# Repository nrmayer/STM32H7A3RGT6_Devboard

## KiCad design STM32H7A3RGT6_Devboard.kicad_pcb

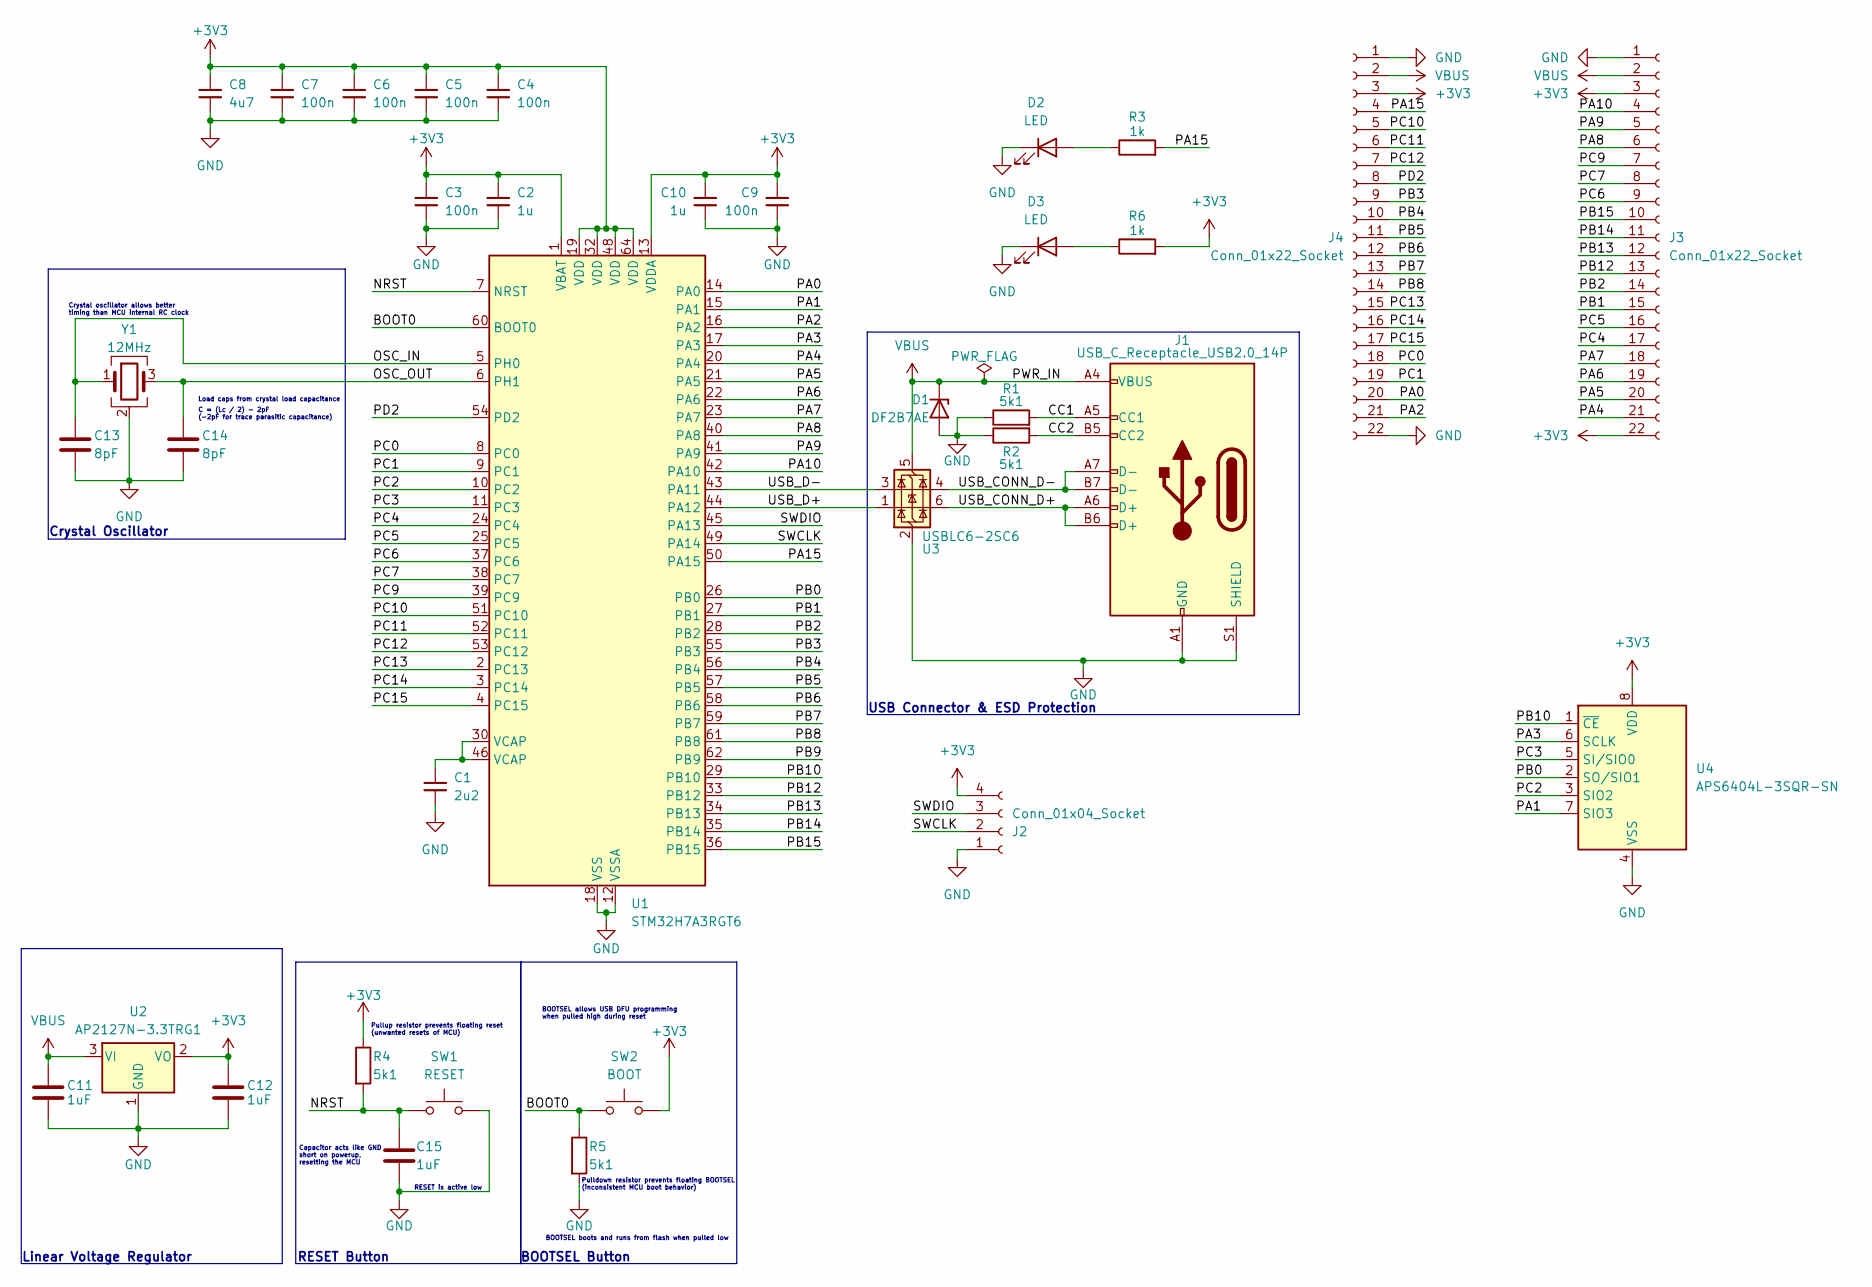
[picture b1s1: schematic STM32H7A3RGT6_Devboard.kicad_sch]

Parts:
C1: 2u2; C_0402_1005Metric_Pad0.74x0.62mm_HandSolder
C2, C10: 1u; C_0603_1608Metric
C3, C4, C5, C6, C7, C9: 100n; C_0402_1005Metric_Pad0.74x0.62mm_HandSolder
C8: 4u7; C_0603_1608Metric
C11, C12: 1uF; C_0402_1005Metric_Pad0.74x0.62mm_HandSolder
C13, C14: 8pF; C_0402_1005Metric_Pad0.74x0.62mm_HandSolder
C15: 1uF; C_0603_1608Metric_Pad1.08x0.95mm_HandSolder
D1: DF2B7AE; D_SOD-523
D2, D3: LED; LED_0603_1608Metric
J1: USB_C_Receptacle_USB2.0_14P; USB_C_Receptacle_Molex_217179-0001
J2: Conn_01x04_Socket; PinHeader_1x04_P2.54mm_Vertical
J3, J4: Conn_01x22_Socket; PinHeader_1x22_P2.54mm_Vertical
R1, R2, R4, R5: 5k1; R_0603_1608Metric
R3, R6: 1k; R_0603_1608Metric_Pad0.98x0.95mm_HandSolder
SW1: RESET; SW_Push_1P1T-SH_NO_CK_KMR2xxG
SW2: BOOT; SW_Push_1P1T-SH_NO_CK_KMR2xxG
U1: STM32H7A3RGT6; LQFP-64_10x10mm_P0.5mm
U2: AP2127N-3.3TRG1; SOT-23
U3: USBLC6-2SC6; SOT-23-6
U4: APS6404L-3SQR-SN; SOIC-8_3.9x4.9mm_P1.27mm
Y1: 12MHz; Crystal_SMD_2016-4Pin_2.0x1.6mm

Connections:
+3V3: C2.1, C3.1, C4.1, C5.1, C6.1, C7.1, C8.1, C9.1, C10.1, C12.1, J2.4, J3.3, J3.22, J4.3, R4.1, R6.2, SW2.2, U1.1 (VBAT), U1.13 (VDDA), U1.19 (VDD), U1.32 (VDD), U1.48 (VDD), U1.64 (VDD), U2.2 (VO), U4.8 (VDD)
/BOOT0: R5.1, SW2.1, U1.60 (BOOT0)
/CC1: J1.A5 (CC1), R1.2
/CC2: J1.B5 (CC2), R2.2
/NRST: C15.1, R4.2, SW1.1, U1.7 (NRST)
/OSC_IN: C13.1, U1.5 (PH0), Y1.1
/OSC_OUT: C14.1, U1.6 (PH1), Y1.3
/PA0: J4.20, U1.14 (PA0)
/PA1: U1.15 (PA1), U4.7 (SIO3)
/PA2: J4.21, U1.16 (PA2)
/PA3: U1.17 (PA3), U4.6 (SCLK)
/PA4: J3.21, U1.20 (PA4)
/PA5: J3.20, U1.21 (PA5)
/PA6: J3.19, U1.22 (PA6)
/PA7: J3.18, U1.23 (PA7)
/PA8: J3.6, U1.40 (PA8)
/PA9: J3.5, U1.41 (PA9)
/PA10: J3.4, U1.42 (PA10)
/PA15: J4.4, R3.2, U1.50 (PA15)
/PB0: U1.26 (PB0), U4.2 (SO/SIO1)
/PB1: J3.15, U1.27 (PB1)
/PB2: J3.14, U1.28 (PB2)
/PB3: J4.9, U1.55 (PB3)
/PB4: J4.10, U1.56 (PB4)
/PB5: J4.11, U1.57 (PB5)
/PB6: J4.12, U1.58 (PB6)
/PB7: J4.13, U1.59 (PB7)
/PB8: J4.14, U1.61 (PB8)
/PB9: U1.62 (PB9)
/PB10: U1.29 (PB10), U4.1 (~CE)
/PB12: J3.13, U1.33 (PB12)
/PB13: J3.12, U1.34 (PB13)
/PB14: J3.11, U1.35 (PB14)
/PB15: J3.10, U1.36 (PB15)
/PC0: J4.18, U1.8 (PC0)
/PC1: J4.19, U1.9 (PC1)
/PC2: U1.10 (PC2), U4.3 (SIO2)
/PC3: U1.11 (PC3), U4.5 (SI/SIO0)
/PC4: J3.17, U1.24 (PC4)
/PC5: J3.16, U1.25 (PC5)
/PC6: J3.9, U1.37 (PC6)
/PC7: J3.8, U1.38 (PC7)
/PC9: J3.7, U1.39 (PC9)
/PC10: J4.5, U1.51 (PC10)
/PC11: J4.6, U1.52 (PC11)
/PC12: J4.7, U1.53 (PC12)
/PC13: J4.15, U1.2 (PC13)
/PC14: J4.16, U1.3 (PC14)
/PC15: J4.17, U1.4 (PC15)
/PD2: J4.8, U1.54 (PD2)
/SWCLK: J2.2, U1.49 (PA14)
/SWDIO: J2.3, U1.45 (PA13)
/USB_CONN_D+: J1.A6 (D+), J1.B6 (D+), U3.6 (I/O1)
/USB_CONN_D-: J1.A7 (D-), J1.B7 (D-), U3.4 (I/O2)
/USB_D+: U1.44 (PA12), U3.1 (I/O1)
/USB_D-: U1.43 (PA11), U3.3 (I/O2)
GND: C1.2, C2.2, C3.2, C4.2, C5.2, C6.2, C7.2, C8.2, C9.2, C10.2, C11.2, C12.2, C13.2, C14.2, C15.2, D1.2 (A), D2.1 (K), D3.1 (K), J1.A1 (GND), J1.A12 (GND), J1.B1 (GND), J1.B12 (GND), J1.S1 (SHIELD), J2.1, J3.1, J4.1, J4.22, R1.1, R2.1, R5.2, SW1.2, U1.12 (VSSA), U1.18 (VSS), U1.31 (VSS), U1.47 (VSS), U1.63 (VSS), U2.1 (GND), U3.2 (GND), U4.4 (VSS), Y1.2 (G), Y1.4 (G)
unnamed: C1.1, U1.30 (VCAP), U1.46 (VCAP)
unnamed: D2.2 (A), R3.1
unnamed: D3.2 (A), R6.1
VBUS: C11.1, D1.1 (K), J1.A4 (VBUS), J1.A9 (VBUS), J1.B4 (VBUS), J1.B9 (VBUS), J3.2, J4.2, U2.3 (VI), U3.5 (VBUS)

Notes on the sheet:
Linear Voltage Regulator
BOOTSEL allows USB DFU programming when pulled high during reset
Load caps from crystal load capacitance
USB Connector & ESD Protection
RESET Button
Capacitor acts like GND short on powerup, resetting the MCU
Pulldown resistor prevents floating BOOTSEL (inconsistent MCU boot behavior)
Crystal Oscillator
C = (Lc / 2) - 2pF (-2pF for trace parasitic capacitance)
BOOTSEL Button
Pullup resistor prevents floating reset (unwanted resets of MCU)
BOOTSEL boots and runs from flash when pulled low
RESET is active low
Crystal oscillator allows better timing than MCU internal RC clock

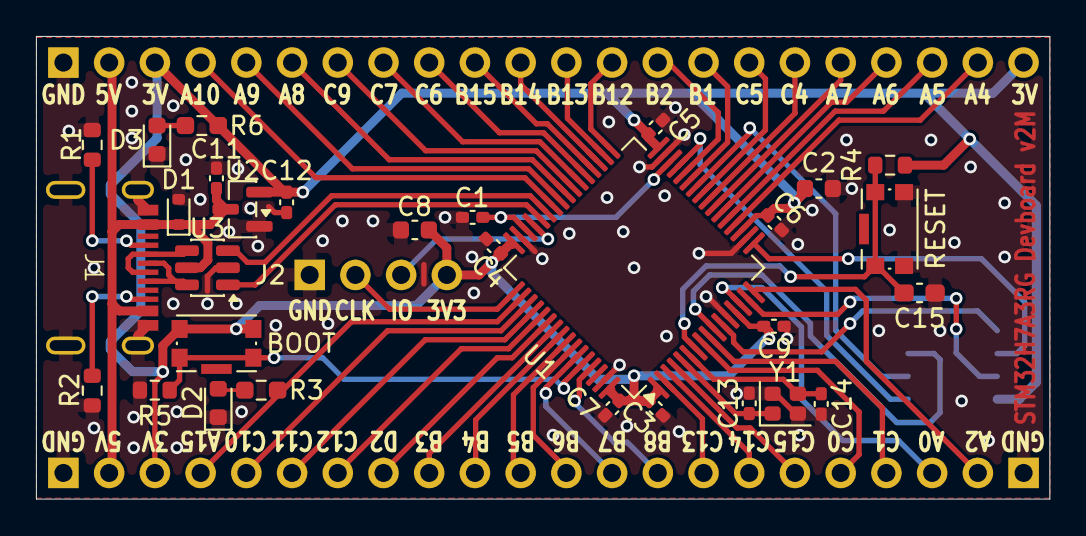
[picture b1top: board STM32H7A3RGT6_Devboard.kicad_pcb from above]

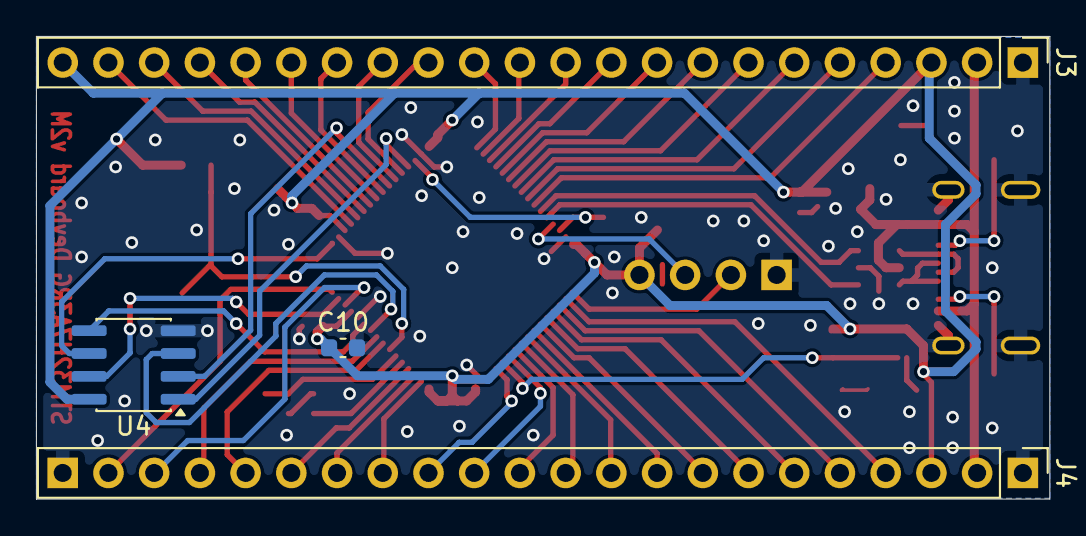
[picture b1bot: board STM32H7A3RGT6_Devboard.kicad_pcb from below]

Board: 2 copper layers, 56.3 x 25.7 mm, 35 parts (4 on the bottom side), 60 nets.
